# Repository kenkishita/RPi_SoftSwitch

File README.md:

RPi Power controller
This board can plug directly to the Raspberry Pi power connector.

Assembling

This board has 8 ports, +V, KA, GND, GND, P2, SWP1, SDP0, and RST. 
But P2 and RST will need connect only when re-programming the U1 (Attiny85).
A momentary switch connects between SWP1 and GND.
SDP0 pin connect to the GPIO23(Top P8) of the Raspberry Pi, and also KA pin to the GPIO24(Top P9) by default.
Any 5V power supply output connect to the +V and GND.

The circuit will auto-detect whether you are configured the SDP0 and KA pin.
After wiring, pressing the button turns the Raspberry Pi on. Then, when you want to turn this off just briefly press the button and the operating system will safely shut down if the connected SDP0 and KA to the specified GPIO.
After the operating system shuts down, the switch will cut the power to the Raspberry Pi.
If holding for the button over 5 seconds will perform force power off with flasshing the LED.
You have to install small script for shutdown functionality in the Raspbian.
Configure the Raspberry Pi
Sample of setup.sh

    echo '#!/bin/bash
    
    #this is the GPIO pin connected to the lead on SDP0
    GPIOpin1=23
    
    #this is the GPIO pin connected to the lead on KA
    GPIOpin2=24

    echo "$GPIOpin1" > /sys/class/gpio/export
    echo "in" > /sys/class/gpio/gpio$GPIOpin1/direction
    echo "$GPIOpin2" > /sys/class/gpio/export
    echo "out" > /sys/class/gpio/gpio$GPIOpin2/direction
    echo "1" > /sys/class/gpio/gpio$GPIOpin2/value
    while [ 1 = 1 ]; do
    power=$(cat /sys/class/gpio/gpio$GPIOpin1/value)
    if [ $power = 0 ]; then
    sleep 1
    else
    sudo poweroff
    fi
    done' > /etc/switch.sh
    sudo chmod 777 /etc/switch.sh
    sudo sed -i '$ i /etc/switch.sh &' /etc/rc.local

License Information

These files are free; you can redistribute them and/or modify them under the
terms of the Creative Commons Attribution-ShareAlike 4.0 International
License only, as published by the Creative Commons organization.

These files are distributed in the hope that they will be useful, but
WITHOUT ANY WARRANTY; without even the implied warranty of MERCHANTABILITY
or FITNESS FOR A PARTICULAR PURPOSE.  See the Creative Commons Attribution-
ShareAlike 4.0 International License for more details.

Please contact Aynik technology Co., Ltd. at kkishita@aynik-tech.jp if you need additional information or have any questions.

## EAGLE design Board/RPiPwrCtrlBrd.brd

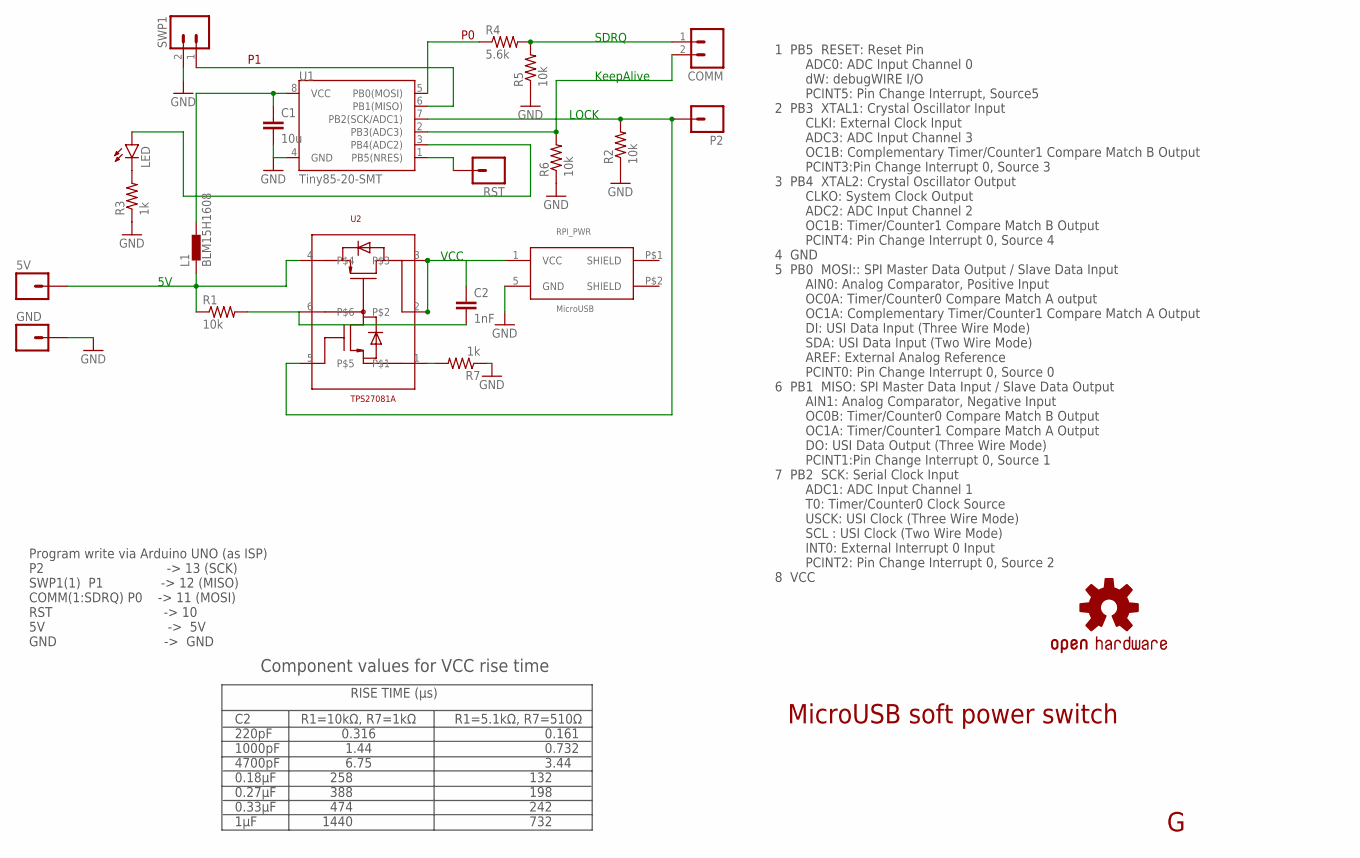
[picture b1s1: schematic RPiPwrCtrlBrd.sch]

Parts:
5V: M01PTH; 1X01
C1: 10u; 1608
C2: 1nF; 1608
COMM: M02PTH; 1X02
GND: M01PTH; 1X01
L1: BLM15H1608; 1608
LED: LED0603; LED-0603
P2: M01PTH; 1X01
R1, R2, R5, R6: 10k; 1608
R3, R7: 1k; 1608
R4: 5.6k; 1608
RPI_PWR: MicroUSB; MICRO-B-THPWR
RST: M01PTH; 1X01
SWP1: M02PTH; 1X02
U1: Tiny85-20-SMT; SO08-EIAJ
U2: TPS27081A; SOT23-6
U$1: OSHW-LOGOS; OSHW-LOGO-S

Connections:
5V: 5V.1, L1.P$1 (1), R1.P$1 (1), U2.4
GND: C1.P$2 (2), GND.1, R2.P$1 (1), R3.P$1 (1), R5.P$1 (1), R6.P$1 (1), R7.P$1 (1), RPI_PWR.5 (GND), SWP1.2, U1.4 (GND)
IN: COMM.2, R6.P$2 (2), U1.2 (PB3(ADC3))
unnamed: C2.P$2 (2), R1.P$2 (2), U2.6
unnamed: LED.C, R3.P$2 (2)
unnamed: LED.A, U1.3 (PB4(ADC2))
unnamed: C1.P$1 (1), L1.P$2 (2), U1.8 (VCC)
unnamed: R7.P$2 (2), U2.1
unnamed: RST.1, U1.1 (PB5(NRES))
OUT: COMM.1, R4.P$2 (2), R5.P$2 (2)
P0: R4.P$1 (1), U1.5 (PB0(MOSI))
P1: SWP1.1, U1.6 (PB1(MISO))
P2: P2.1, R2.P$2 (2), U1.7 (PB2(SCK/ADC1)), U2.5
VCC: C2.P$1 (1), RPI_PWR.1 (VCC), U2.2, U2.3

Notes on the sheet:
SDRQ
KeepAlive
LOCK
VCC
Component values for VCC rise time
RISE TIME (µs)
C2 R1=10kΩ, R7=1kΩ R1=5.1kΩ, R7=510Ω 220pF 0.316 0.161 1000pF 1.44 0.732 4700pF 6.75 3.44 0.18µF 258 132 0.27µF 388 198 0.33µF 474 242 1µF 1440 732
MicroUSB soft power switch
1 PB5 RESET: Reset Pin ADC0: ADC Input Channel 0 dW: debugWIRE I/O PCINT5: Pin Change Interrupt, Source5 2 PB3 XTAL1: Crystal Oscillator Input CLKI: External Clock Input ADC3: ADC Input Channel 3 OC1B: Complementary Timer/Counter1 Compare Match B Output PCINT3:Pin Change Interrupt 0, Source 3 3 PB4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
Program write via Arduino UNO (as ISP) P2 -> 13 (SCK) SWP1(1) P1 -> 12 (MISO) COMM(1:SDRQ) P0 -> 11 (MOSI) RST -> 10 5V -> 5V GND -> GND

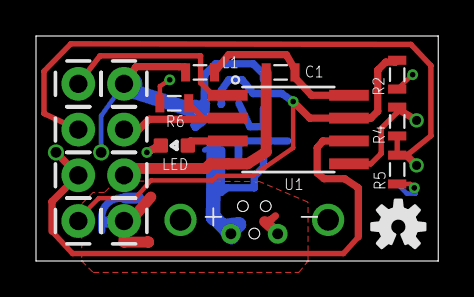
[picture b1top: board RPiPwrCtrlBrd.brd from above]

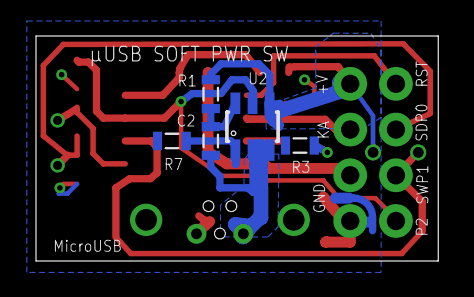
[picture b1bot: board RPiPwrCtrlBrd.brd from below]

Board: 2 copper layers, 22.3 x 12.5 mm, 21 parts (5 on the bottom side), 14 nets.

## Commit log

2016-05-21 add picture of the board layout
2016-05-22 change LED output from digital to analog (PWM) for easy checking the status

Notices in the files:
parts and their libraries:
SparkFun-DigitalIC: Licensing: Creative Commons ShareAlike 4.0 International - https://creativecommons.org/licenses/by-sa/4.0
SparkFun: Licensing: CC v3.0 Share-Alike You are welcome to use this library for commercial purposes.
